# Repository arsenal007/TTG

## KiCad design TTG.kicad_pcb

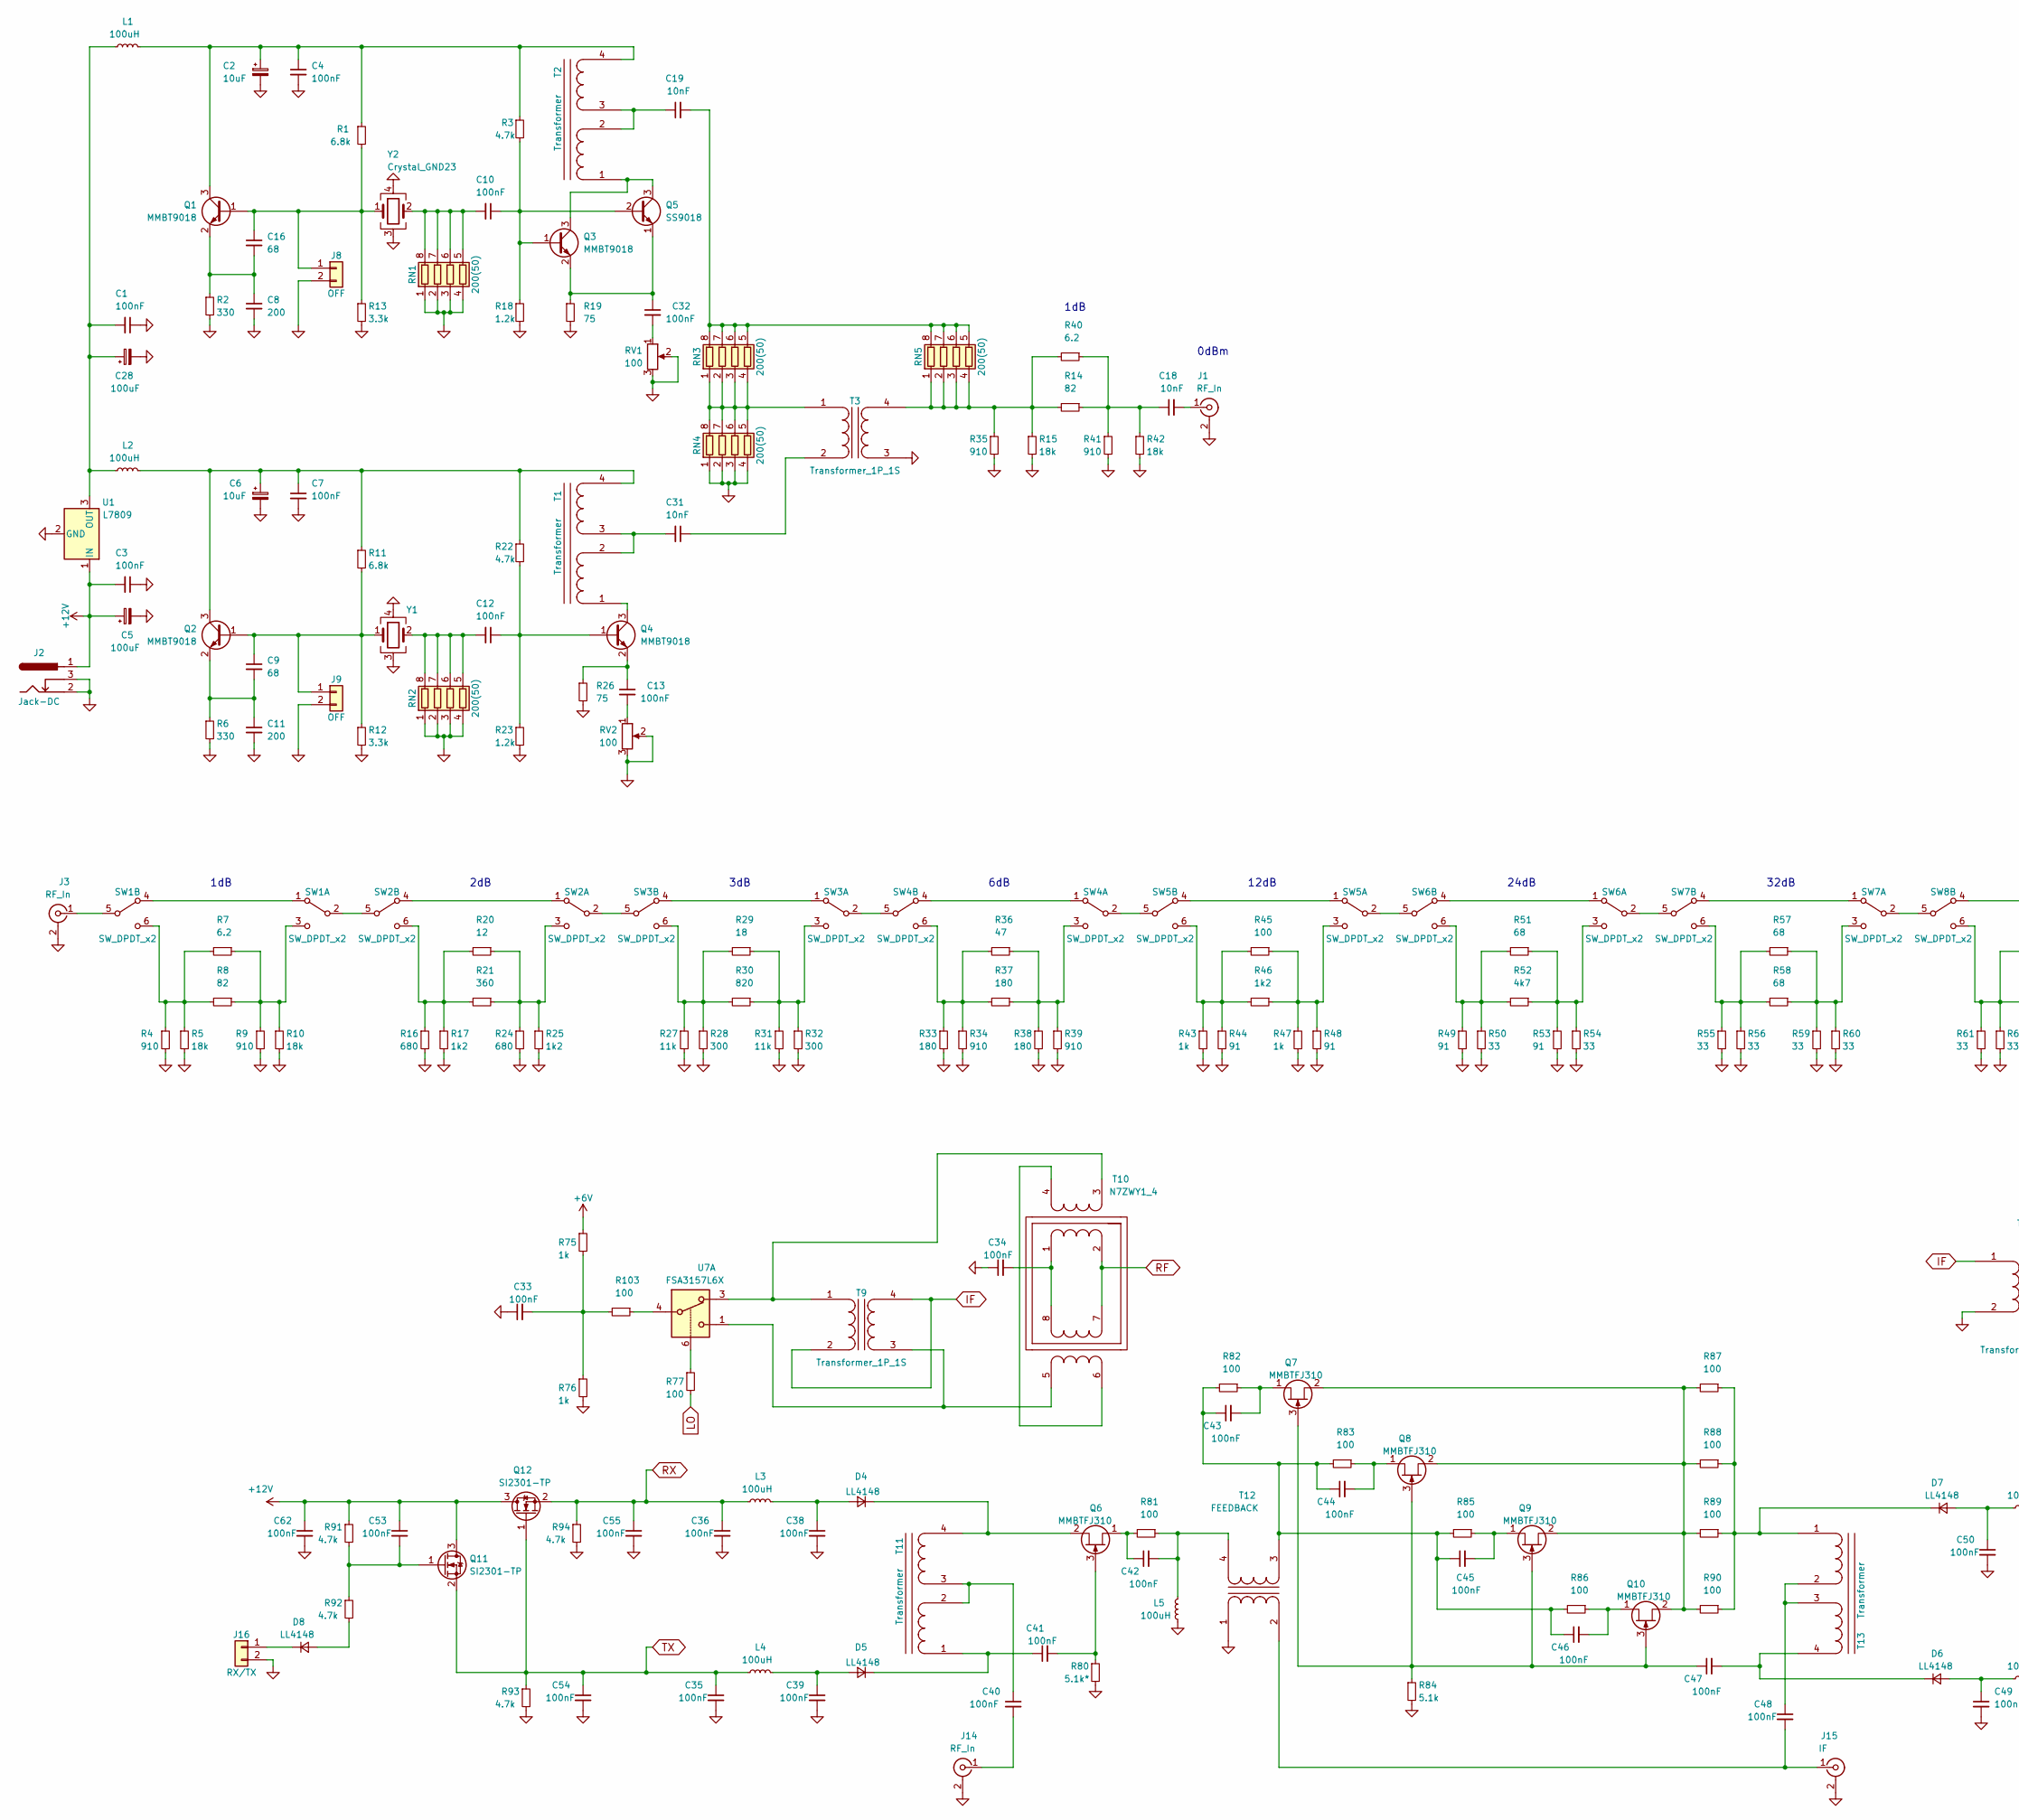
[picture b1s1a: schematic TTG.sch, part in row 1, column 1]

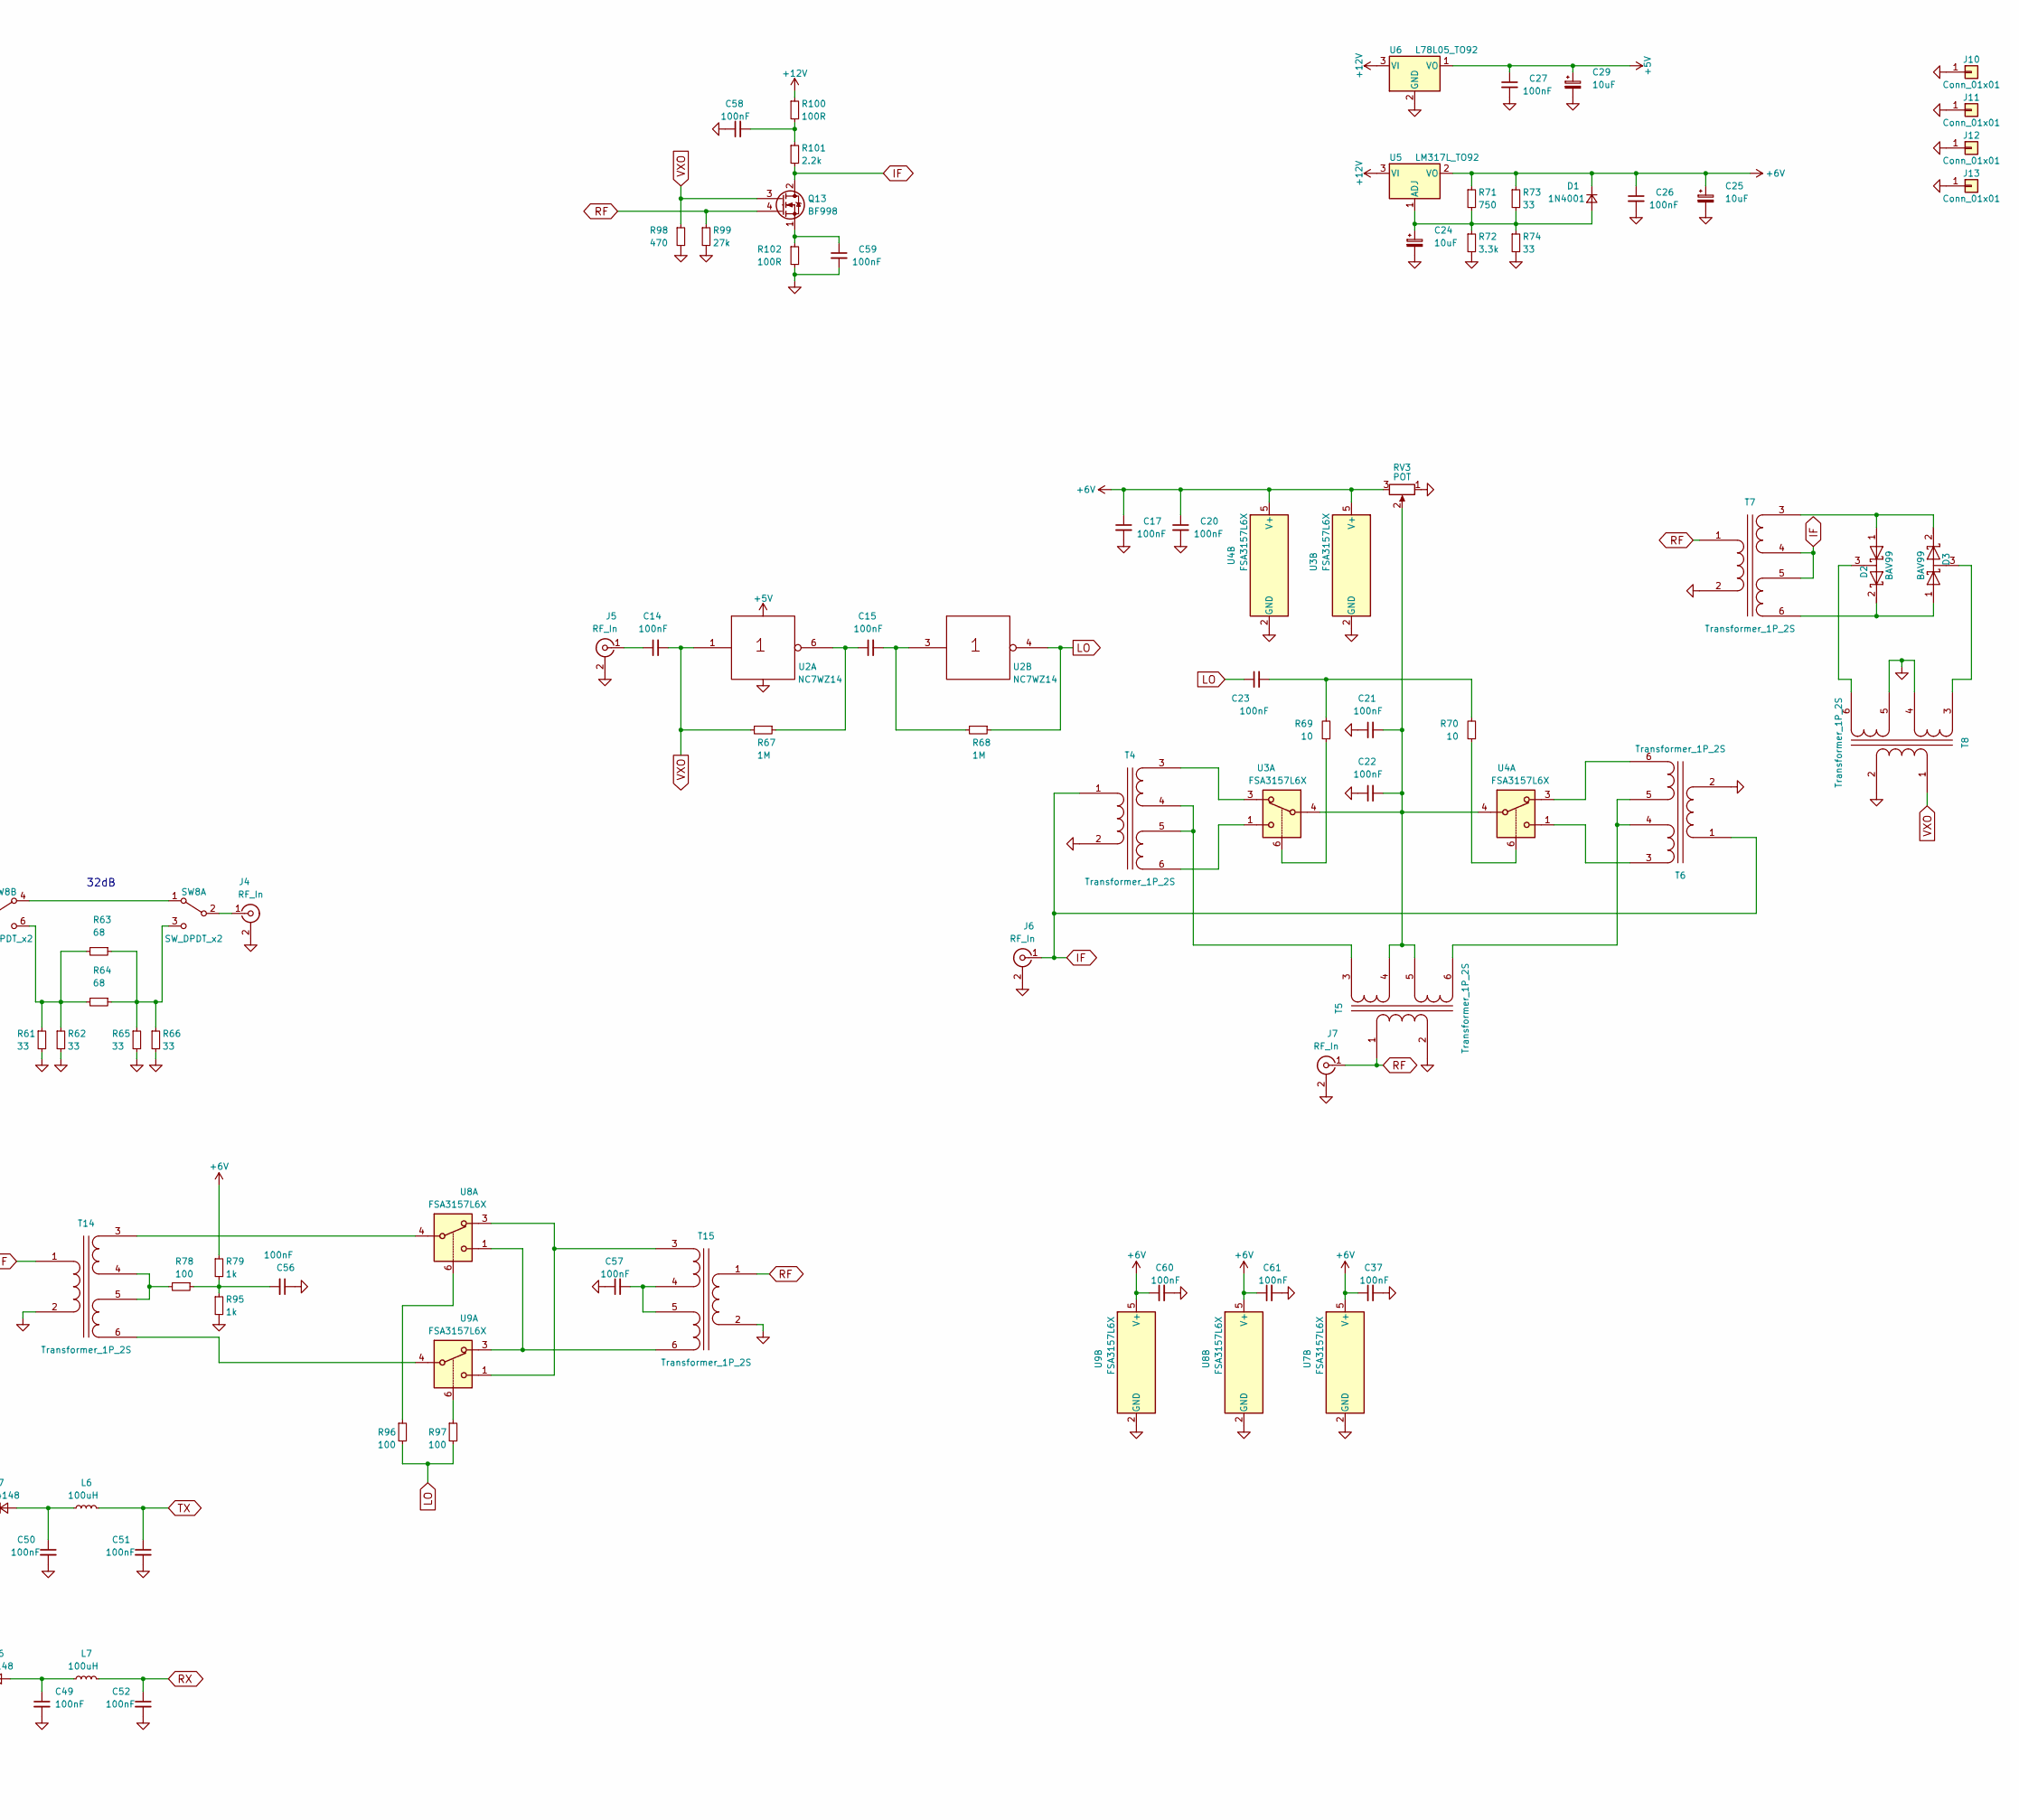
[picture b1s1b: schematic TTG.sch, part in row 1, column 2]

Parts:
C1, C3, C4, C7, C10, C12, C13, C15, C17, C20, C21, C22, C23, C26, C27, C32, C33, C34, C35, C36, C37, C38, C39, C40, C41, C42, C43, C44, C45, C46, C47, C48, C49, C50, C51, C52, C53, C54, C55, C56, C57, C58, C59, C60, C61, C62: 100nF; C_1206_0603
C2, C6, C24, C25, C29: 10uF; CP_Tantalum_Case-A_EIA-3216-18_Hand
C5, C28: 100uF; CP_Tantalum_Case-D_EIA-7343-31_Hand
C8, C11: 200; C_1206_0603
C9, C16: 68; C_1206_0603
C14: 100nF; C_1206_HandSoldering
C18, C19, C31: 10nF; C_1206_0603
D1: 1N4001; D_DO-41_SOD81_P7.62mm_Horizontal
D2, D3: BAV99; SOT-23_Handsoldering
D4, D5, D6, D7, D8: LL4148; D_MiniMELF_Handsoldering
J1, J3, J4, J5, J6, J7, J14: RF_In; RFCONNECTOR
J2: Jack-DC; BARREL_JACK
J8, J9: OFF; Pin_Header_Straight_1x02_Pitch2.54mm
J10, J11, J12, J13: Conn_01x01; MountingHole_3.2mm_M3_DIN965_Pad
J15: IF; RFCONNECTOR
J16: RX/TX; Pin_Header_Straight_1x02_Pitch2.54mm
L1, L2, L3, L4, L5, L6, L7: 100uH; R_Axial_DIN0204_L3.6mm_D1.6mm_P7.62mm_Horizontal
Q1, Q2, Q3, Q4: MMBT9018; SOT-23_Handsoldering
Q5: SS9018; TO-92_Horizontal1_Molded_Narrow
Q6, Q7, Q8, Q9, Q10: MMBTFJ310; SOT-23_Handsoldering
Q11, Q12: SI2301-TP; SOT-23_Handsoldering
Q13: BF998; SOT-143_Handsoldering
R1, R11: 6.8k; R_1206_0603
R2, R6: 330; R_1206_0603
R3, R22, R91, R92, R93, R94: 4.7k; R_1206_0603
R4, R9, R34, R35, R39, R41: 910; R_1206_0603
R5, R10, R15, R42: 18k; R_1206_0603
R7, R40: 6.2; R_1206_0603
R8, R14: 82; R_1206_0603
R12, R13, R72: 3.3k; R_1206_0603
R16, R24: 680; R_1206_0603
R17, R25, R46: 1k2; R_1206_0603
R18, R23: 1.2k; R_1206_0603
R19, R26: 75; R_1206_0603
R20: 12; R_1206_0603
R21: 360; R_1206_0603
R27, R31: 11k; R_1206_0603
R28, R32: 300; R_1206_0603
R29: 18; R_1206_0603
R30: 820; R_1206_0603
R33, R37, R38: 180; R_1206_0603
R36: 47; R_1206_0603
R43, R47, R75, R76, R79, R95: 1k; R_1206_0603
R44, R48, R49, R53: 91; R_1206_0603
R45, R77, R78, R81, R82, R83, R85, R86, R87, R88, R89, R90, R96, R97, R103: 100; R_1206_0603
R50, R54, R55, R56, R59, R60, R61, R62, R65, R66, R73, R74: 33; R_1206_0603
R51, R57, R58, R63, R64: 68; R_1206_0603
R52: 4k7; R_1206_0603
R67, R68: 1M; R_1206_0603
R69, R70: 10; R_1206_0603
R71: 750; R_1206_0603
R80: 5.1k*; R_1206_0603
R84: 5.1k; R_1206_0603
R98: 470; R_1206_0603
R99: 27k; R_1206_0603
R100, R102: 100R; R_1206_0603
R101: 2.2k; R_1206_HandSoldering
RN1, RN2, RN3, RN4, RN5: 200(50); R_Array_Concave_4x0603
RV1, RV2: 100; Potentiometer_Trimmer_Piher_PT-6v_Horizontal
RV3: POT; Potentiometer_Trimmer_Piher_PT-6v_Horizontal
SW1, SW2, SW3, SW4, SW5, SW6, SW7, SW8: SW_DPDT_x2; SW_CuK_JS202011CQN_DPDT_Straight
T1, T2, T11, T13: Transformer; TF14
T3, T9: Transformer_1P_1S; TF14
T4, T5, T6, T7, T8, T14, T15: Transformer_1P_2S; HF_transf3
T10: N7ZWY1_4; N7ZWY
T12: FEEDBACK; TF_2
U1: L7809; TO-220-3_Horizontal
U2: NC7WZ14; SOT-363_SC-70-6_Handsoldering
U3, U4, U7, U8, U9: FSA3157L6X; SOT-363_SC-70-6_Handsoldering
U5: LM317L_TO92; TO-92_Horizontal1_Molded_Narrow
U6: L78L05_TO92; TO-92_Horizontal1_Molded_Narrow
Y1, Y2: Crystal_GND23; Crystal_HC49-U_Vertical

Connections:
+5V: C27.1, C29.1, U2.5 (Vcc), U6.1 (VO)
+6V: C17.1, C20.1, C25.1, C26.1, C37.1, C60.1, C61.1, D1.1 (K), R71.1, R73.1, R75.1, R79.1, RV3.3, U3.5 (V+), U4.5 (V+), U5.2 (VO), U7.5 (V+), U8.5 (V+), U9.5 (V+)
+12V: C3.2, C5.1, C53.1, C62.1, J2.1, Q11.3 (D), Q12.3 (D), R91.1, R100.1, U1.1 (IN), U5.3 (VI), U6.3 (VI)
GND: C1.1, C2.2, C3.1, C4.2, C5.2, C6.2, C7.2, C8.2, C11.2, C17.2, C20.2, C21.1, C22.1, C24.2, C25.2, C26.2, C27.2, C28.2, C29.2, C33.1, C34.1, C35.2, C36.2, C37.2, C38.2, C39.2, C49.2, C50.2, C51.2, C52.2, C54.2, C55.2, C56.1, C57.1, C58.1, C59.2, C60.2, C61.2, C62.2, J1.2 (Ext), J2.2, J2.3, J3.2 (Ext), J4.2 (Ext), J5.2 (Ext), J6.2 (Ext), J7.2 (Ext), J8.2, J9.2, J10.1, J11.1, J12.1, J13.1, J14.2 (Ext), J15.2 (Ext), J16.2, L5.1, R2.2, R4.2, R5.2, R6.2, R9.2, R10.2, R12.2, R13.2, R15.2, R16.2, R17.2, R18.2, R19.2, R23.2, R24.2, R25.2, R26.2, R27.2, R28.2, R31.2, R32.2, R33.2, R34.2, R35.2, R38.2, R39.2, R41.2, R42.2, R43.2, R44.2, R47.2, R48.2, R49.2, R50.2, R53.2, R54.2, R55.2, R56.2, R59.2, R60.2, R61.2, R62.2, R65.2, R66.2, R72.2, R74.2, R76.2, R80.2, R84.2, R93.2, R94.2, R95.2, R98.2, R99.2, R102.2, RN1.1 (R1.1), RN1.2 (R2.1), RN1.3 (R3.1), RN1.4 (R4.1), RN2.1 (R1.1), RN2.2 (R2.1), RN2.3 (R3.1), RN2.4 (R4.1), RN4.1 (R1.1), RN4.2 (R2.1), RN4.3 (R3.1), RN4.4 (R4.1), RV1.2, RV1.3, RV2.2, RV2.3, RV3.1, T3.3 (SA), T4.2 (AB), T5.2 (AB), T6.2 (AB), T7.2 (AB), T8.2 (AB), T8.4 (SB), T8.5 (SC), T12.1 (AA), T14.2 (AB), T15.2 (AB), U1.2 (GND), U2.2 (Gnd), U3.2 (GND), U4.2 (GND), U6.2 (GND), U7.2 (GND), U8.2 (GND), U9.2 (GND), Y1.3, Y1.4, Y2.3, Y2.4
IF: J6.1 (In), Q13.2 (D), R101.2, T4.1 (AA), T6.1 (AA), T7.4 (SB), T7.5 (SC), T9.2 (AB), T9.4 (SB), T14.1 (AA)
LO: C23.1, R68.1, R77.2, R96.2, R97.2, U2.4
unnamed: C1.2, C28.1, L1.1, L2.1, U1.3 (OUT)
unnamed: C2.1, C4.1, L1.2, Q1.3 (C), R1.1, R3.1, T2.4 (SA)
unnamed: C6.1, C7.1, L2.2, Q2.3 (C), R11.1, R22.1, T1.4 (SA)
unnamed: C9.1, J9.1, Q2.1 (B), R11.2, R12.1, Y1.1
unnamed: C10.1, Q3.1 (B), Q5.2 (B), R3.2, R18.1
unnamed: C10.2, RN1.5 (R4.2), RN1.6 (R3.2), RN1.7 (R2.2), RN1.8 (R1.2), Y2.2
unnamed: C9.2, C11.1, Q2.2 (E), R6.1
unnamed: C12.1, Q4.1 (B), R22.2, R23.1
unnamed: C12.2, RN2.5 (R4.2), RN2.6 (R3.2), RN2.7 (R2.2), RN2.8 (R1.2), Y1.2
unnamed: C13.1, Q4.2 (E), R26.1
unnamed: C13.2, RV2.1
unnamed: C14.1, J5.1 (In)
unnamed: C15.1, R67.1, U2.6
unnamed: C15.2, R68.2, U2.3
unnamed: C16.1, J8.1, Q1.1 (B), R1.2, R13.1, Y2.1
unnamed: C8.1, C16.2, Q1.2 (E), R2.1
unnamed: C18.1, R14.1, R40.1, R41.1, R42.1
unnamed: C18.2, J1.1 (In)
unnamed: C19.1, T2.2 (AB), T2.3 (SB)
unnamed: C19.2, RN3.5 (R4.2), RN3.6 (R3.2), RN3.7 (R2.2), RN3.8 (R1.2), RN5.5 (R4.2), RN5.6 (R3.2), RN5.7 (R2.2), RN5.8 (R1.2)
unnamed: C21.2, C22.2, RV3.2, T5.4 (SB), T5.5 (SC), U3.4, U4.4
unnamed: C23.2, R69.2, R70.2
unnamed: C24.1, D1.2 (A), R71.2, R72.1, R73.2, R74.1, U5.1 (ADJ)
unnamed: C31.1, T3.2 (AB)
unnamed: C31.2, T1.2 (AB), T1.3 (SB)
unnamed: C32.1, Q3.2 (E), Q5.1 (E), R19.1
unnamed: C32.2, RV1.1
unnamed: C33.2, R75.2, R76.1, R103.2
unnamed: C34.2, T10.1, T10.8
unnamed: C38.1, D4.2 (A), L3.2
unnamed: C39.1, D5.2 (A), L4.2
unnamed: C40.1, T11.2 (AB), T11.3 (SB)
unnamed: C40.2, J14.1 (In)
unnamed: C41.1, D5.1 (K), T11.1 (AA)
unnamed: C41.2, Q6.3 (G), R80.1
unnamed: C42.1, Q6.1 (D), R81.2
unnamed: C42.2, L5.2, R81.1, T12.4 (SB)
unnamed: C43.1, C44.1, C45.1, C46.1, R82.2, R83.2, R85.2, R86.2, T12.3 (SA)
unnamed: C43.2, Q7.1 (D), R82.1
unnamed: C44.2, Q8.1 (D), R83.1
unnamed: C45.2, Q9.1 (D), R85.1
unnamed: C46.2, Q10.1 (D), R86.1
unnamed: C47.1, Q7.3 (G), Q8.3 (G), Q9.3 (G), Q10.3 (G), R84.1
unnamed: C47.2, D6.1 (K), T13.4 (SA)
unnamed: C48.1, T13.2 (AB), T13.3 (SB)
unnamed: C48.2, J15.1 (In), T12.2 (AB)
unnamed: C49.1, D6.2 (A), L7.1
unnamed: C50.1, D7.2 (A), L6.1
unnamed: C53.2, Q11.1 (G), R91.2, R92.1
unnamed: C56.2, R78.1, R79.2, R95.1
unnamed: C57.2, T15.4 (SB), T15.5 (SC)
unnamed: C58.2, R100.2, R101.1
unnamed: C59.1, Q13.1 (S), R102.1
unnamed: D2.1 (A), D3.2 (K), T7.3 (SA)
unnamed: D2.2 (K), D3.1 (A), T7.6 (SD)
unnamed: D2.3 (common), T8.6 (SD)
unnamed: D3.3 (common), T8.3 (SA)
unnamed: D4.1 (K), Q6.2 (S), T11.4 (SA)
unnamed: D7.1 (K), R87.1, R88.1, R89.1, R90.1, T13.1 (AA)
unnamed: D8.1 (K), J16.1
unnamed: D8.2 (A), R92.2
unnamed: J3.1 (In), SW1.5 (B)
unnamed: J4.1 (In), SW8.2 (B)
unnamed: Q3.3 (C), Q5.3 (C), T2.1 (AA)
unnamed: Q4.3 (C), T1.1 (AA)
unnamed: Q7.2 (S), Q8.2 (S), Q9.2 (S), Q10.2 (S), R87.2, R88.2, R89.2, R90.2
unnamed: R4.1, R5.1, R7.2, R8.2, SW1.6 (C)
unnamed: R7.1, R8.1, R9.1, R10.1, SW1.3 (C)
unnamed: R14.2, R15.1, R35.1, R40.2, RN5.1 (R1.1), RN5.2 (R2.1), RN5.3 (R3.1), RN5.4 (R4.1), T3.4 (SB)
unnamed: R16.1, R17.1, R20.2, R21.2, SW2.6 (C)
unnamed: R20.1, R21.1, R24.1, R25.1, SW2.3 (C)
unnamed: R27.1, R28.1, R29.2, R30.2, SW3.6 (C)
unnamed: R29.1, R30.1, R31.1, R32.1, SW3.3 (C)
unnamed: R33.1, R34.1, R36.2, R37.2, SW4.6 (C)
unnamed: R36.1, R37.1, R38.1, R39.1, SW4.3 (C)
unnamed: R43.1, R44.1, R45.2, R46.2, SW5.6 (C)
unnamed: R45.1, R46.1, R47.1, R48.1, SW5.3 (C)
unnamed: R49.1, R50.1, R51.2, R52.2, SW6.6 (C)
unnamed: R51.1, R52.1, R53.1, R54.1, SW6.3 (C)
unnamed: R55.1, R56.1, R57.2, R58.2, SW7.6 (C)
unnamed: R57.1, R58.1, R59.1, R60.1, SW7.3 (C)
unnamed: R61.1, R62.1, R63.2, R64.2, SW8.6 (C)
unnamed: R63.1, R64.1, R65.1, R66.1, SW8.3 (C)
unnamed: R69.1, U3.6
unnamed: R70.1, U4.6
unnamed: R77.1, U7.6
unnamed: R78.2, T14.4 (SB), T14.5 (SC)
unnamed: R96.1, U8.6
unnamed: R97.1, U9.6
unnamed: R103.1, U7.4
unnamed: RN3.1 (R1.1), RN3.2 (R2.1), RN3.3 (R3.1), RN3.4 (R4.1), RN4.5 (R4.2), RN4.6 (R3.2), RN4.7 (R2.2), RN4.8 (R1.2), T3.1 (AA)
unnamed: SW1.1 (A), SW1.4 (A)
unnamed: SW1.2 (B), SW2.5 (B)
unnamed: SW2.1 (A), SW2.4 (A)
unnamed: SW2.2 (B), SW3.5 (B)
unnamed: SW3.1 (A), SW3.4 (A)
unnamed: SW3.2 (B), SW4.5 (B)
unnamed: SW4.1 (A), SW4.4 (A)
unnamed: SW4.2 (B), SW5.5 (B)
unnamed: SW5.1 (A), SW5.4 (A)
unnamed: SW5.2 (B), SW6.5 (B)
unnamed: SW6.1 (A), SW6.4 (A)
unnamed: SW6.2 (B), SW7.5 (B)
unnamed: SW7.1 (A), SW7.4 (A)
unnamed: SW7.2 (B), SW8.5 (B)
unnamed: SW8.1 (A), SW8.4 (A)
unnamed: T4.3 (SA), U3.3
unnamed: T4.4 (SB), T4.5 (SC), T5.3 (SA)
unnamed: T4.6 (SD), U3.1
unnamed: T5.6 (SD), T6.4 (SB), T6.5 (SC)
unnamed: T6.3 (SA), U4.1
unnamed: T6.6 (SD), U4.3
unnamed: T9.1 (AA), T10.3, U7.3
unnamed: T10.4, T10.6
unnamed: T9.3 (SA), T10.5, U7.1
unnamed: T14.3 (SA), U8.4
unnamed: T14.6 (SD), U9.4
unnamed: T15.3 (SA), U8.3, U9.1
unnamed: T15.6 (SD), U8.1, U9.3
RF: J7.1 (In), Q13.4 (G1), R99.1, T5.1 (AA), T7.1 (AA), T10.2, T10.7, T15.1 (AA)
RX: C36.1, C52.1, C55.1, L3.1, L7.2, Q12.2 (S), R94.1
TX: C35.1, C51.1, C54.1, L4.1, L6.2, Q11.2 (S), Q12.1 (G), R93.1
VXO: C14.2, Q13.3 (G2), R67.2, R98.1, T8.1 (AA), U2.1

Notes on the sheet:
1dB
2dB
3dB
6dB
12dB
24dB
32dB
0dBm

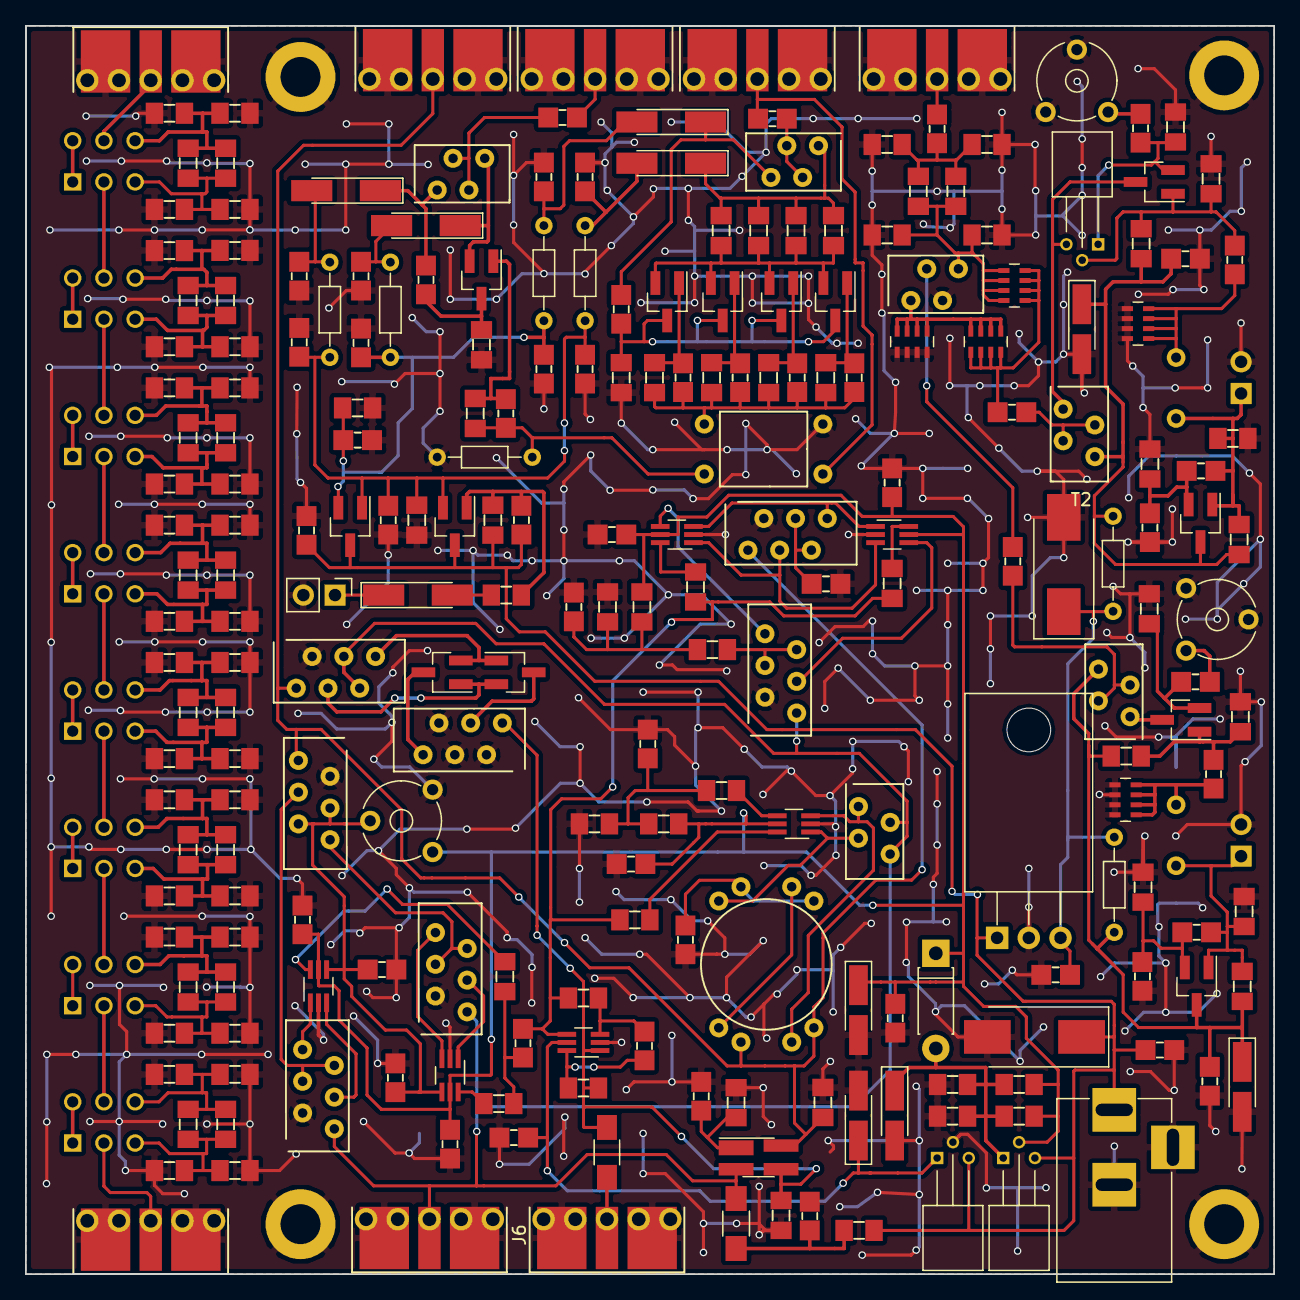
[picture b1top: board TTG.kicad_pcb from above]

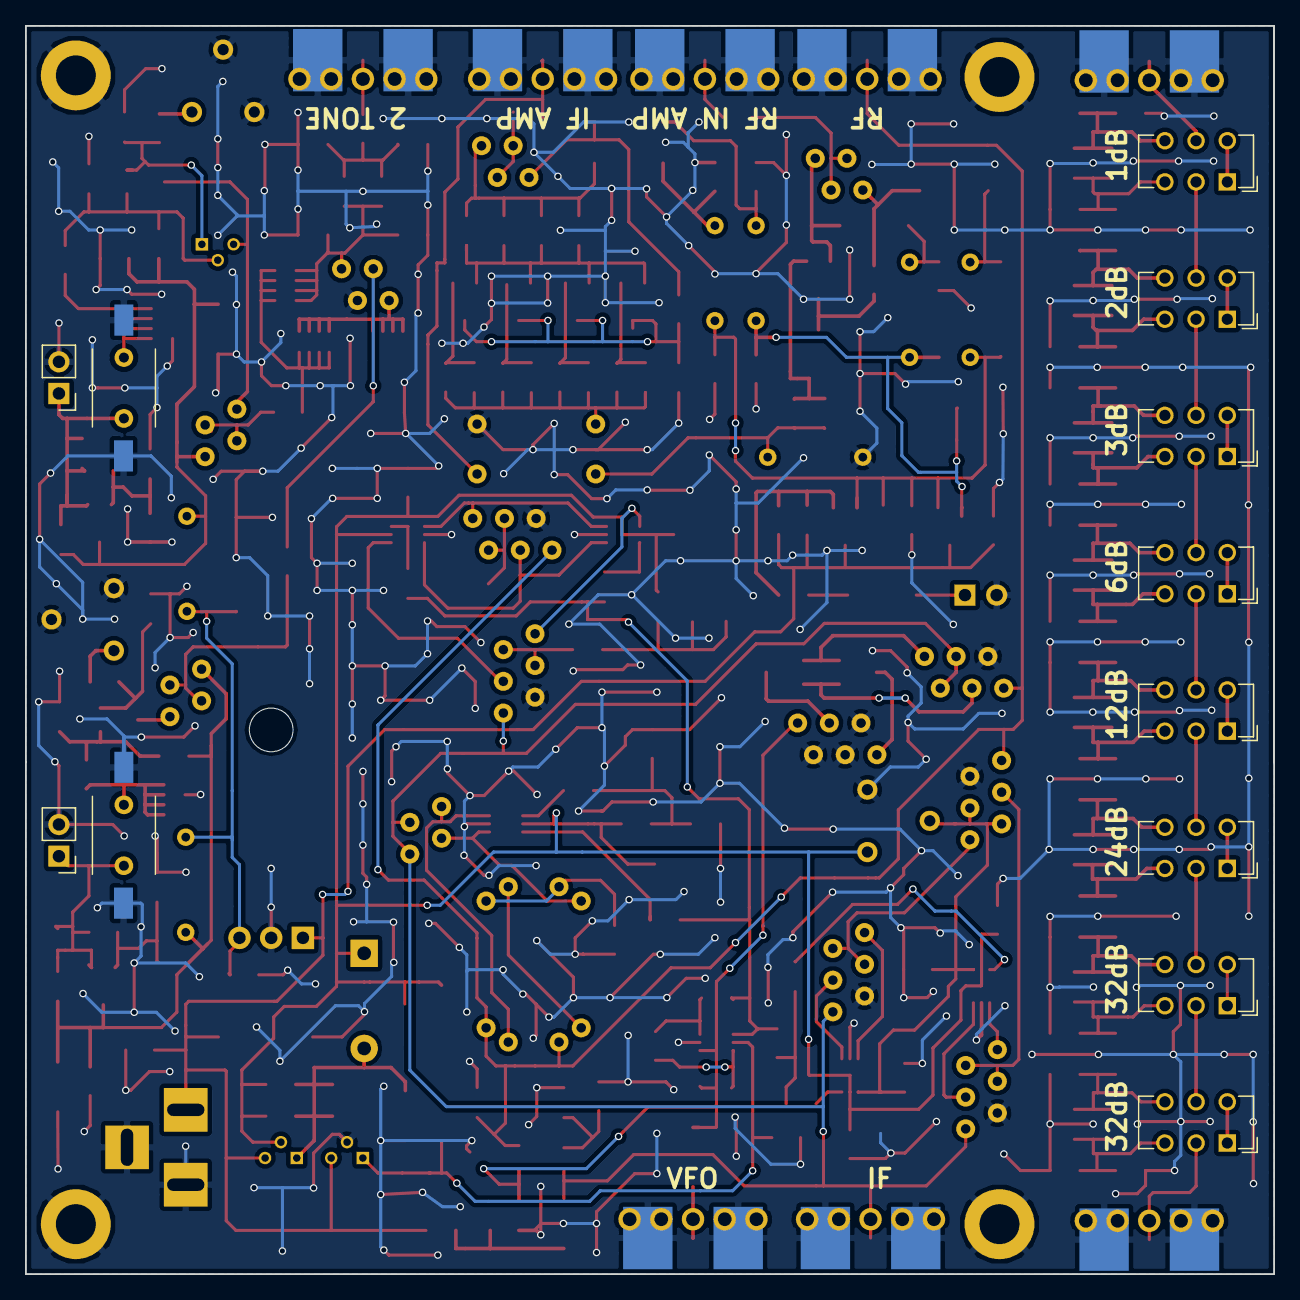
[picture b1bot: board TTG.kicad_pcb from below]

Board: 2 copper layers, 100.0 x 100.0 mm, 250 parts (12 on the bottom side), 129 nets.

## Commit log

2019-05-11 SC2314
2019-06-10 release, no rasin mixer
2019-07-21 att fixed values
2019-08-15 attenuators values update
